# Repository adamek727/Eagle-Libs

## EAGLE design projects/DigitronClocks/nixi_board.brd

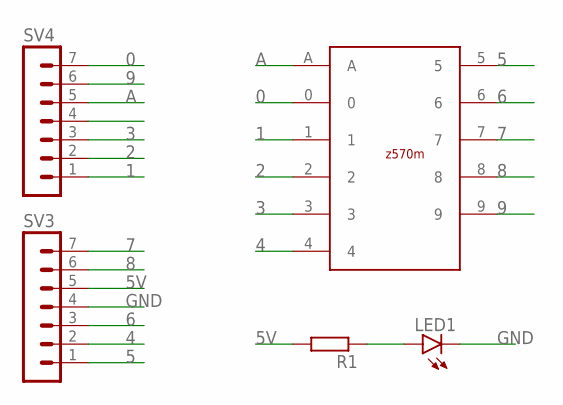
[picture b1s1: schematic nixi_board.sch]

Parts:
LED1: LEDSMT1206; 1206
R1: R-EU_R1206; R1206
SV3, SV4: MA07-1
U$1: Z570M

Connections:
0: SV4.7, U$1.0
1: SV4.1, U$1.1
2: SV4.2, U$1.2
3: SV4.3, U$1.3
4: SV3.2, U$1.4
5: SV3.1, U$1.5
5V: R1.2, SV3.5
6: SV3.3, U$1.6
7: SV3.7, U$1.7
8: SV3.6, U$1.8
9: SV4.6, U$1.9
A: SV4.5, U$1.A
GND: LED1.C, SV3.4
unnamed: LED1.A, R1.1

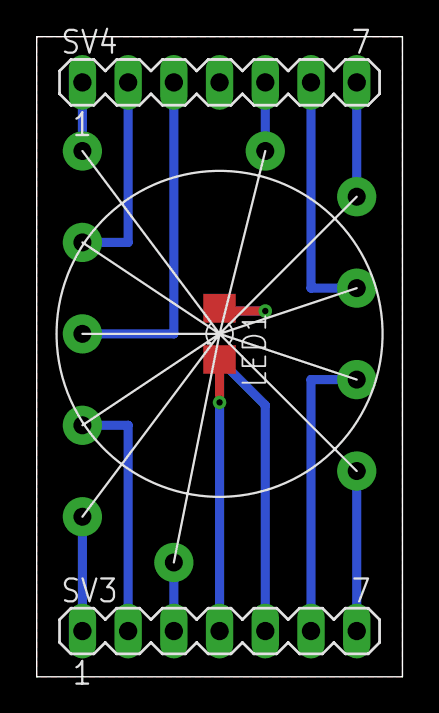
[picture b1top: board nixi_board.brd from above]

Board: 2 copper layers, 20.3 x 35.6 mm, 5 parts (1 on the bottom side), 14 nets.

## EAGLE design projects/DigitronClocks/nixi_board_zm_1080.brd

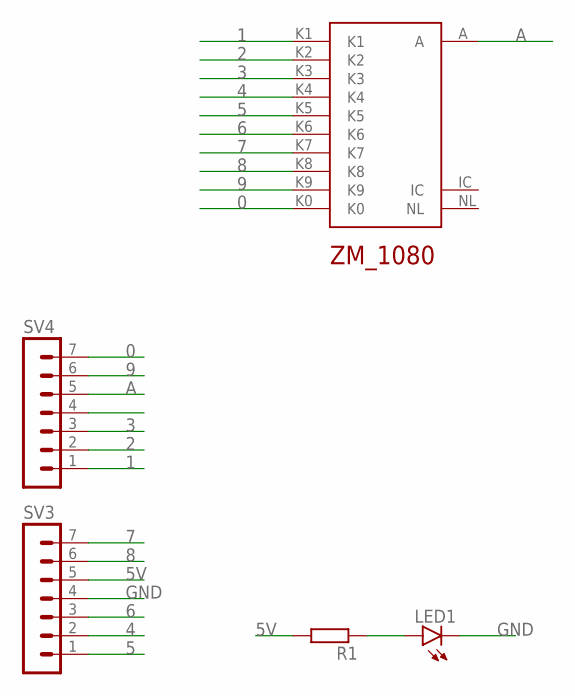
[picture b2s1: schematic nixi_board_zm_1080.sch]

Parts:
LED1: LEDSMT1206; 1206
R1: R-EU_R1206; R1206
SV3, SV4: MA07-1
U$2: ZM_1080

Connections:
0: SV4.7, U$2.K0
1: SV4.1, U$2.K1
2: SV4.2, U$2.K2
3: SV4.3, U$2.K3
4: SV3.2, U$2.K4
5: SV3.1, U$2.K5
5V: R1.2, SV3.5
6: SV3.3, U$2.K6
7: SV3.7, U$2.K7
8: SV3.6, U$2.K8
9: SV4.6, U$2.K9
A: SV4.5, U$2.A
GND: LED1.C, SV3.4
unnamed: LED1.A, R1.1

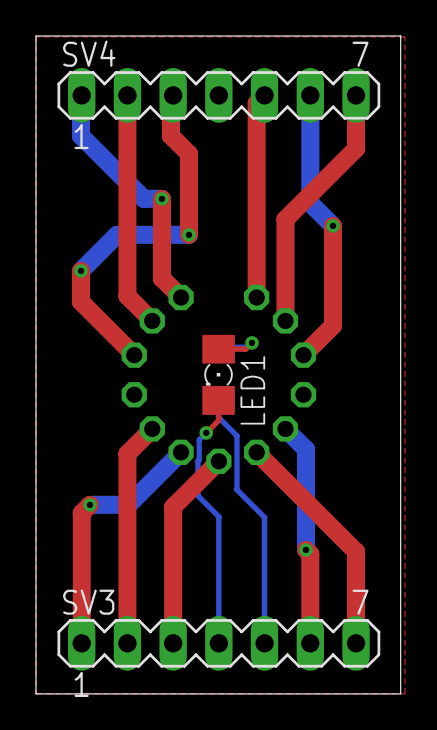
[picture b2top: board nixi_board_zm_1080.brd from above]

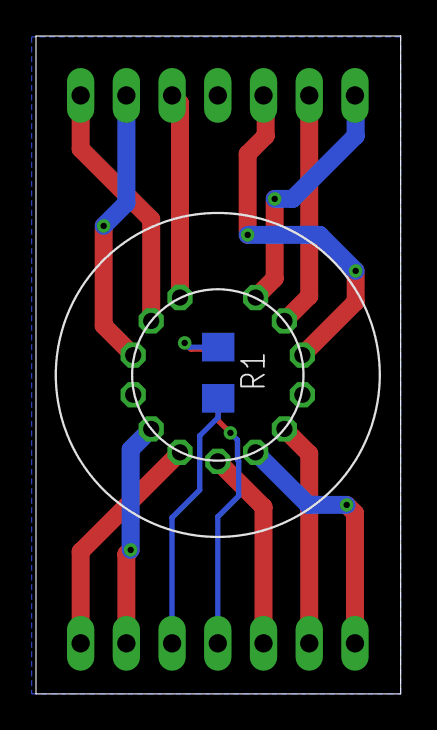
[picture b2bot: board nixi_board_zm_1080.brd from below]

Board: 2 copper layers, 20.3 x 36.5 mm, 5 parts (2 on the bottom side), 14 nets.

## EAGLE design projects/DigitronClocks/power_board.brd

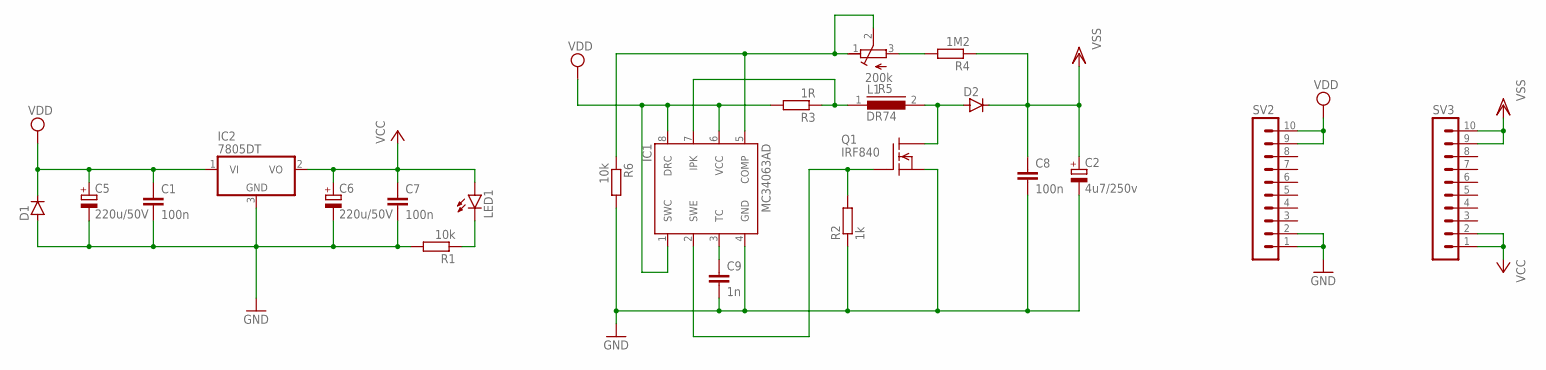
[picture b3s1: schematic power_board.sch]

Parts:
C1, C7, C8: 100n; C1206
C2: 4u7/250v; E5-10,5
C5, C6: 220u/50V; 153CLV-1010
C9: 1n; C1206
D1, D2: D-SOD-80; SOD80
IC1: MC34063AD; SO08
IC2: 7805DT; TO252
L1: DR74
LED1: LEDSMT1206; 1206
Q1: IRF840; TO220
R1, R6: 10k; R1206
R2: 1k; R1206
R3: 1R; R1206
R4: 1M2; R1206
R5: 200k; RTRIM43P
SV2, SV3: MA10-1

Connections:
GND: C1.2, C2.-, C5.-, C6.-, C7.2, C8.2, C9.2, D1.2 (A), IC1.4 (GND), IC2.3 (GND), Q1.3 (S), R1.2, R2.1, R6.2, SV2.1, SV2.2
unnamed: LED1.C, R1.1
unnamed: IC1.5 (COMP), R5.1 (E), R5.2 (S), R6.1
unnamed: IC1.7 (IPK), L1.1, R3.1
unnamed: D2.2 (A), L1.2, Q1.2 (D)
unnamed: C9.1, IC1.3 (TC)
unnamed: IC1.2 (SWE), Q1.1 (G), R2.2
unnamed: R4.2, R5.3 (A)
VCC: C6.+, C7.1, IC2.2 (VO), LED1.A, SV3.1, SV3.2
VDD: C1.1, C5.+, D1.1 (C), IC1.1 (SWC), IC1.6 (VCC), IC1.8 (DRC), IC2.1 (VI), R3.2, SV2.9, SV2.10
VSS: C2.+, C8.1, D2.1 (C), R4.1, SV3.9, SV3.10

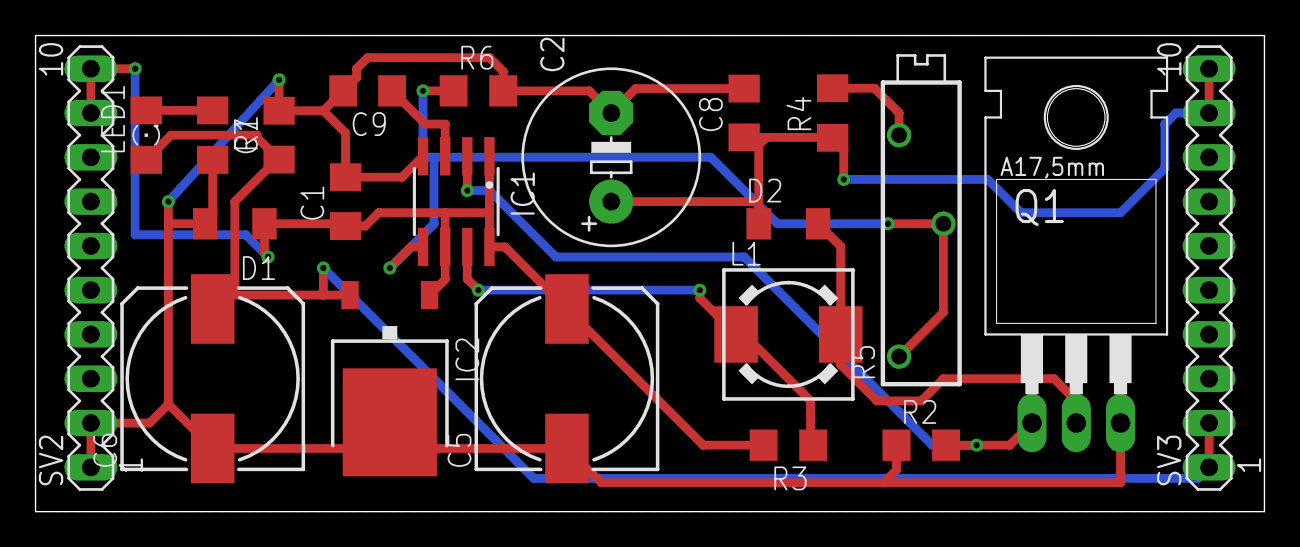
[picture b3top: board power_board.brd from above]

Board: 2 copper layers, 70.5 x 27.3 mm, 22 parts (0 on the bottom side), 11 nets.

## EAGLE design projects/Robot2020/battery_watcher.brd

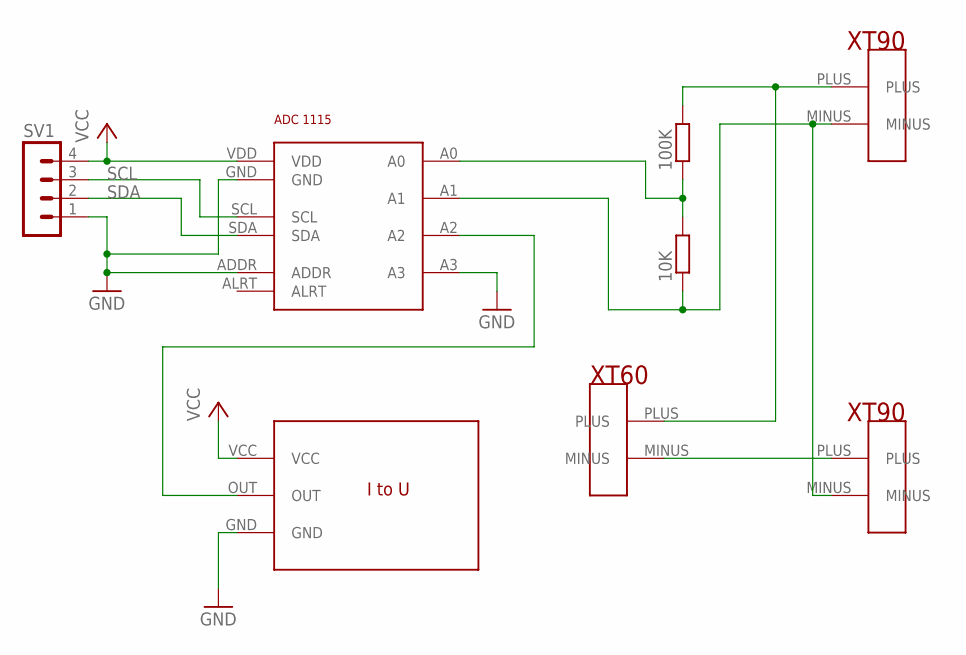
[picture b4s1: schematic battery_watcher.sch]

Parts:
10K, 100K: R-EU_M1206; M1206
SV1: MA04-1
U$1: ADC1115
U$2: I2U_MODULE; I2U
U$3, U$4: XT90
U$5: XT60

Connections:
GND: SV1.1, U$1.A3, U$1.ADDR, U$1.GND, U$2.GND
unnamed: U$1.A2, U$2.OUT
unnamed: 10K.2, 100K.1, U$1.A0
unnamed: 100K.2, U$4.PLUS, U$5.PLUS
unnamed: 10K.1, U$1.A1, U$3.MINUS, U$4.MINUS
unnamed: U$3.PLUS, U$5.MINUS
SCL: SV1.3, U$1.SCL
SDA: SV1.2, U$1.SDA
VCC: SV1.4, U$1.VDD, U$2.VCC

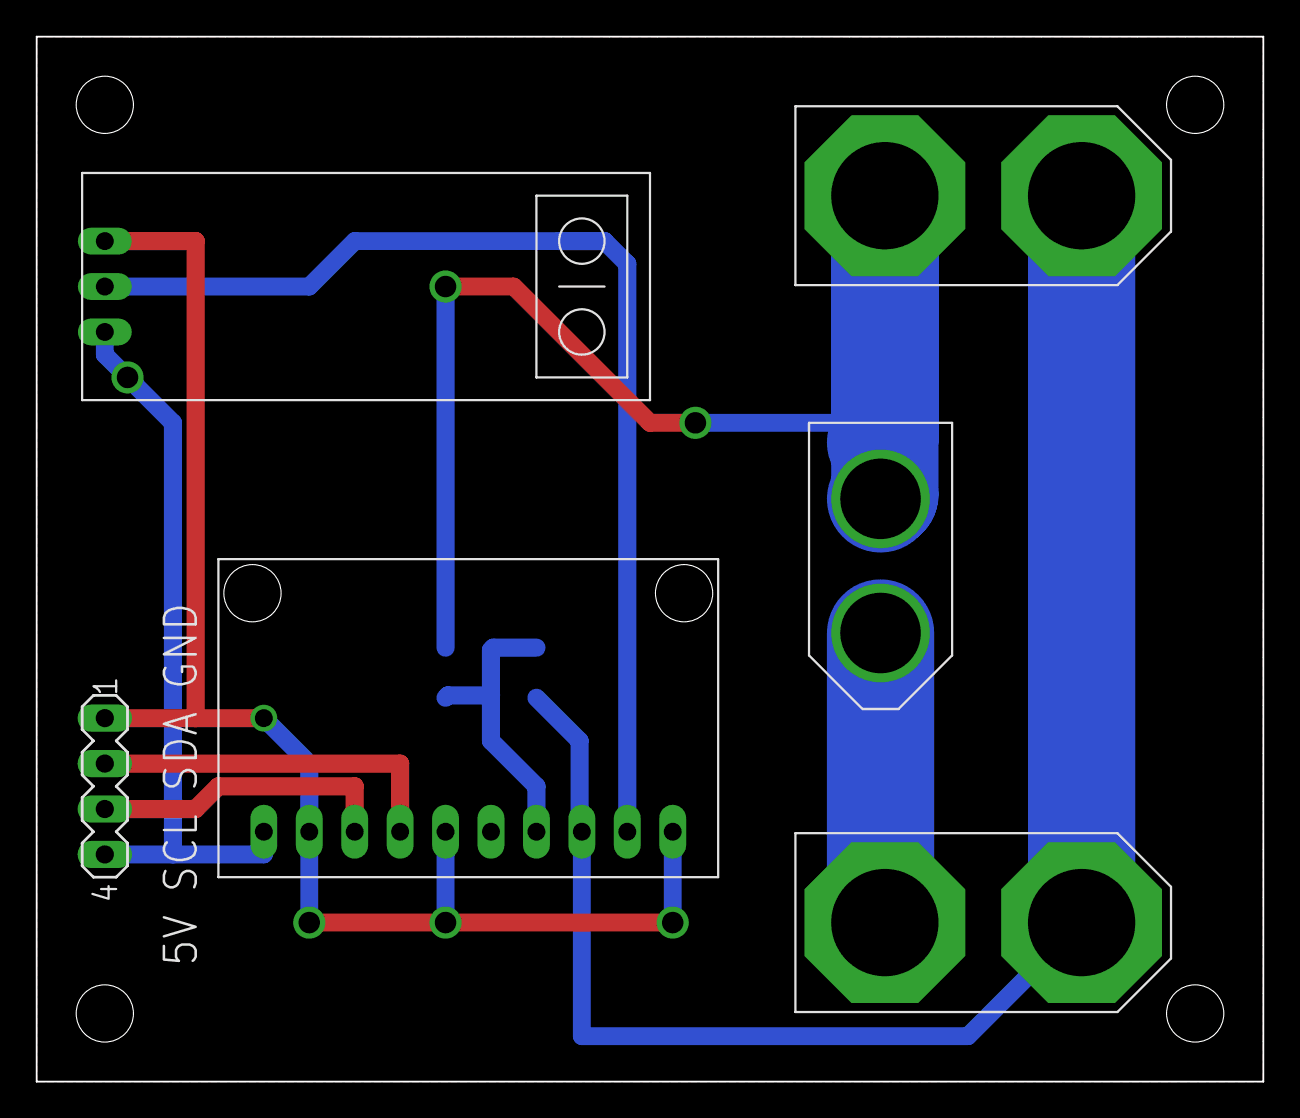
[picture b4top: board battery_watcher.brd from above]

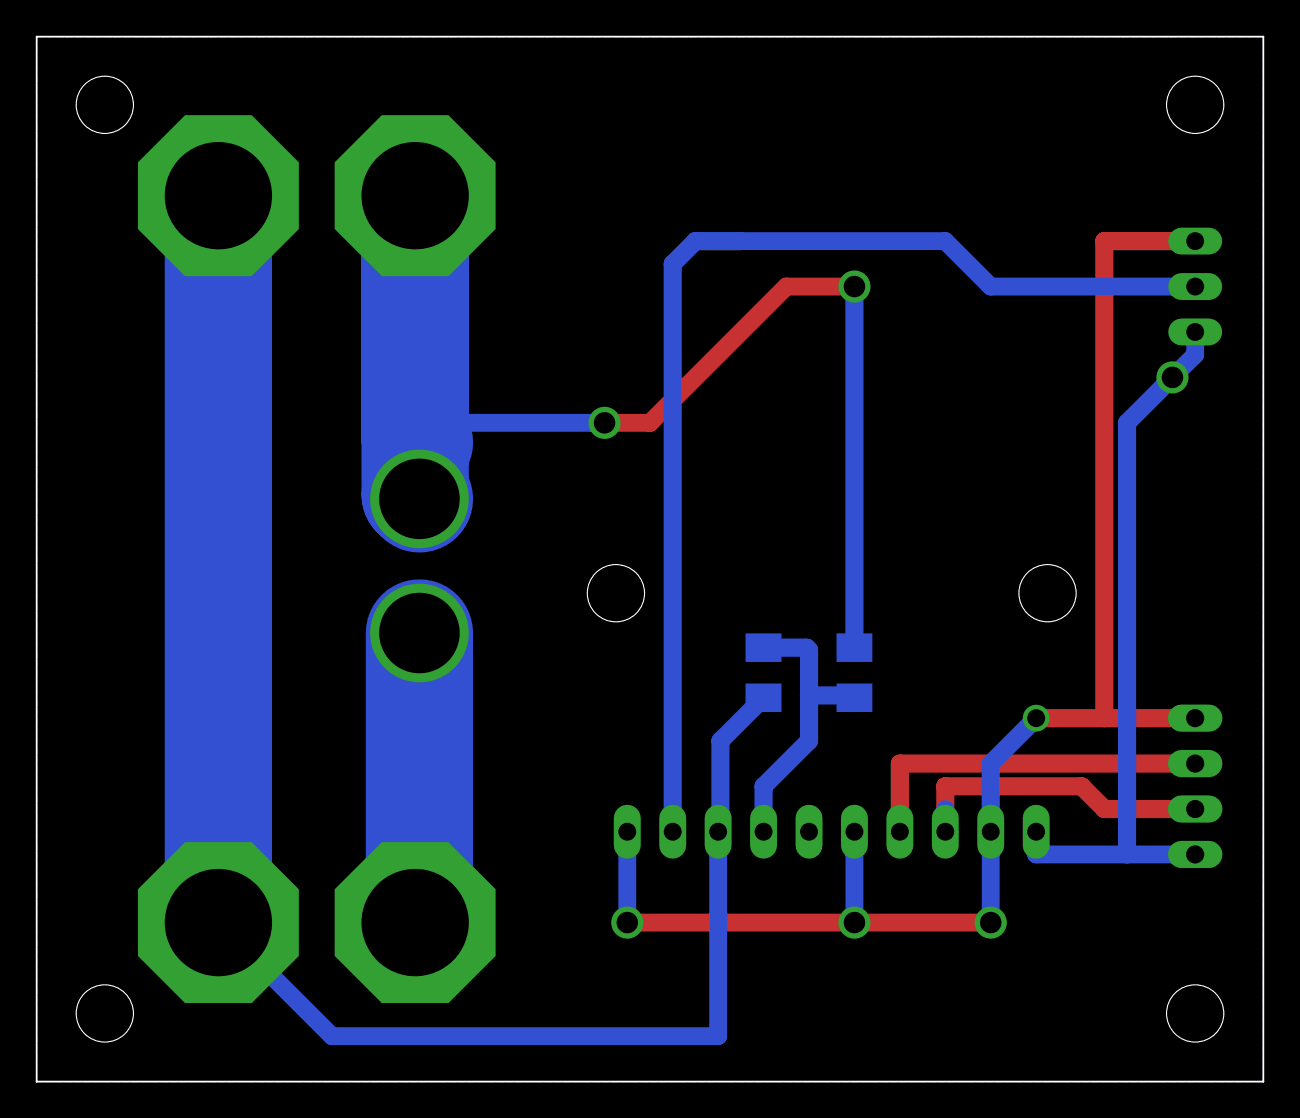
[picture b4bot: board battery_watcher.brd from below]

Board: 2 copper layers, 68.6 x 58.4 mm, 8 parts (2 on the bottom side), 9 nets.

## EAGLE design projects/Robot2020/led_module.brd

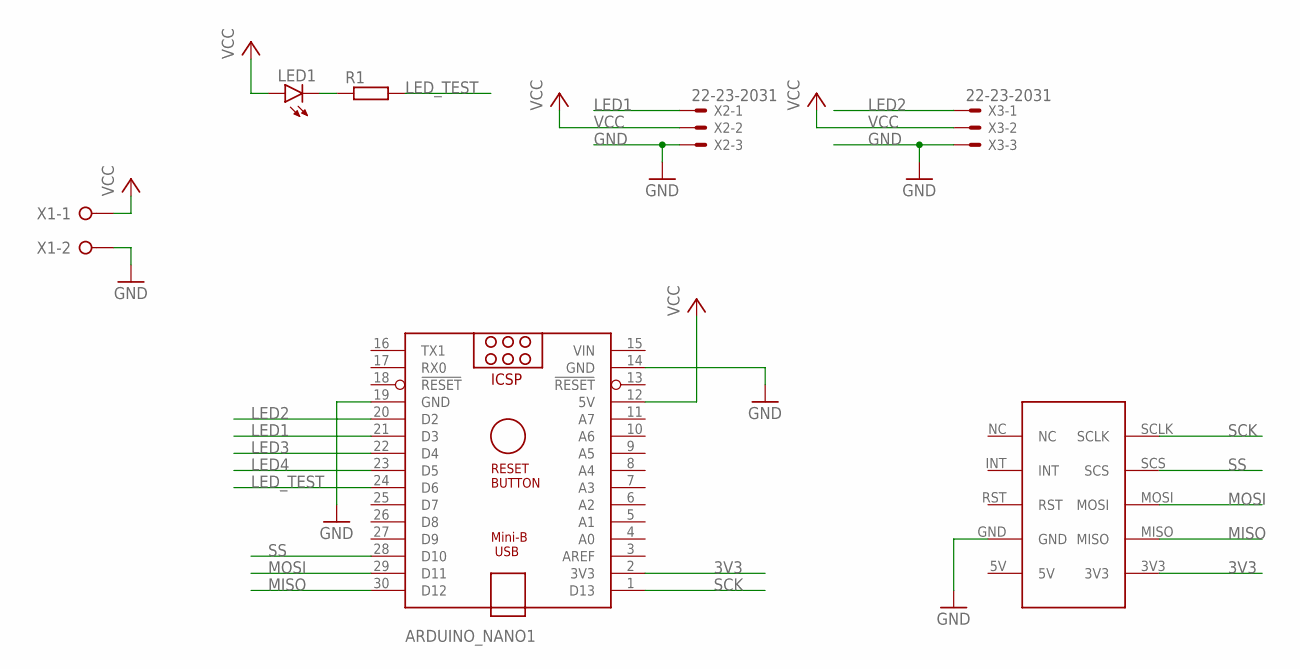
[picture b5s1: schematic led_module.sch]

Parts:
ARDUINO_NANO1: ARDUINO_NANO
LED1: LEDSML1206; SML1206
R1: R-EU_M1206; M1206
U$1: W5500_MODULE
X1: W237-02P; W237-132
X2, X3: 22-23-2031

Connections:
3V3: ARDUINO_NANO1.2 (3V3), U$1.3V3
GND: ARDUINO_NANO1.14 (GND), ARDUINO_NANO1.19 (GND), U$1.GND, X1.2, X2.3, X3.3
LED1: ARDUINO_NANO1.21 (D3), X2.1
LED2: ARDUINO_NANO1.20 (D2), X3.1
LED3: ARDUINO_NANO1.22 (D4)
LED4: ARDUINO_NANO1.23 (D5)
LED_TEST: ARDUINO_NANO1.24 (D6), R1.2
MISO: ARDUINO_NANO1.30 (D12), U$1.MISO
MOSI: ARDUINO_NANO1.29 (D11), U$1.MOSI
unnamed: LED1.C, R1.1
SCK: ARDUINO_NANO1.1 (D13), U$1.SCLK
SS: ARDUINO_NANO1.28 (D10), U$1.SCS
VCC: ARDUINO_NANO1.12 (5V), LED1.A, X1.1, X2.2, X3.2
VIN: ARDUINO_NANO1.15 (VIN)

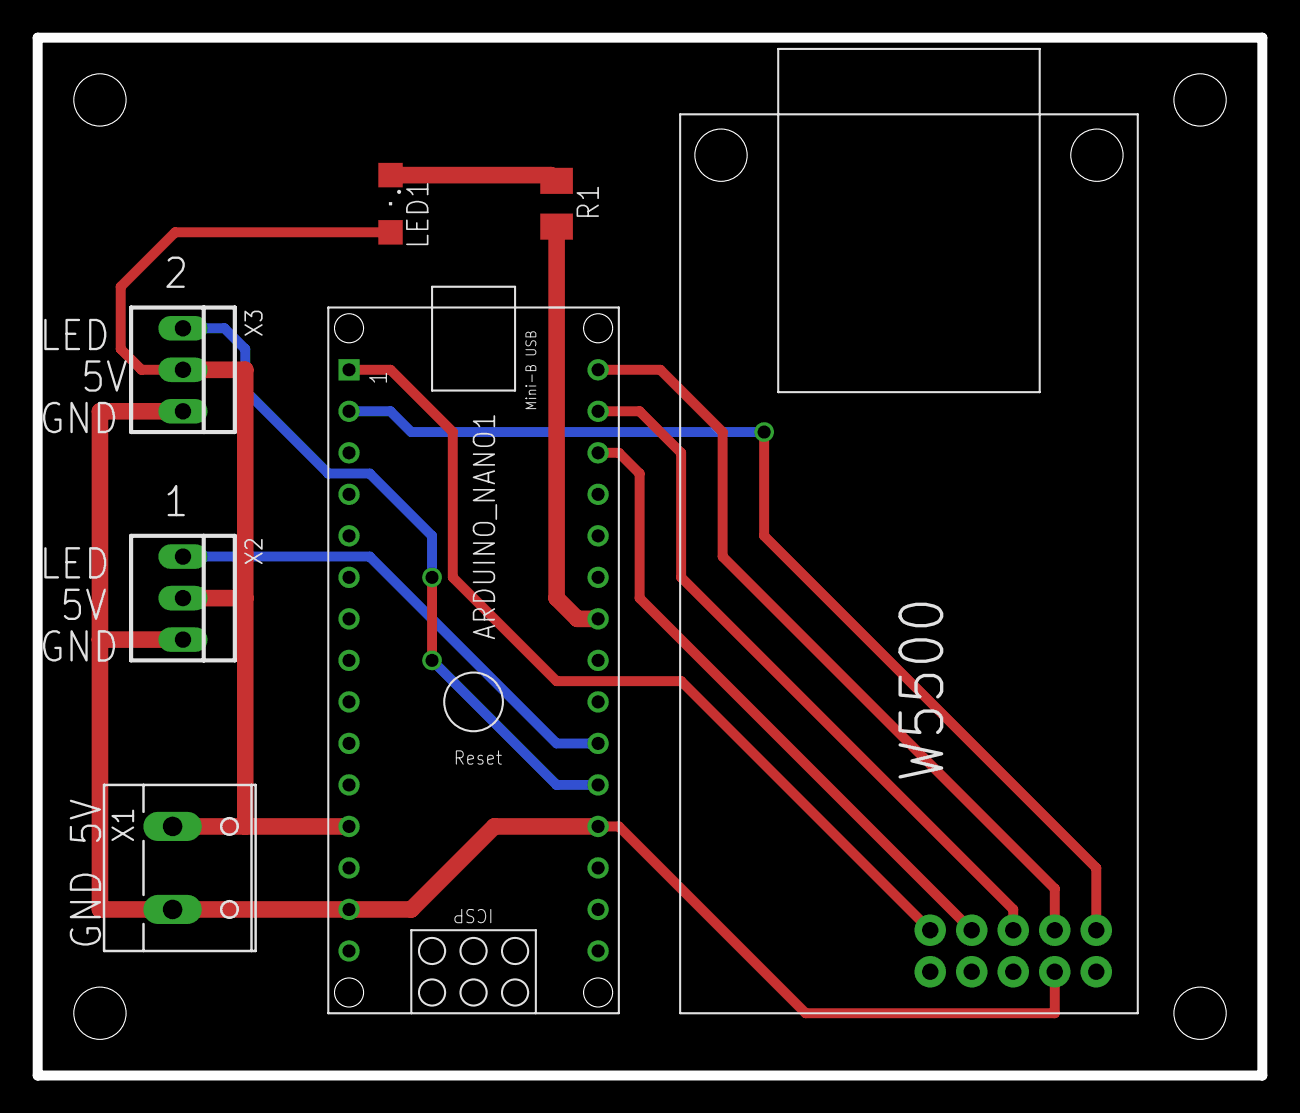
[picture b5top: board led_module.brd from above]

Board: 2 copper layers, 74.9 x 63.5 mm, 7 parts (0 on the bottom side), 11 nets.
